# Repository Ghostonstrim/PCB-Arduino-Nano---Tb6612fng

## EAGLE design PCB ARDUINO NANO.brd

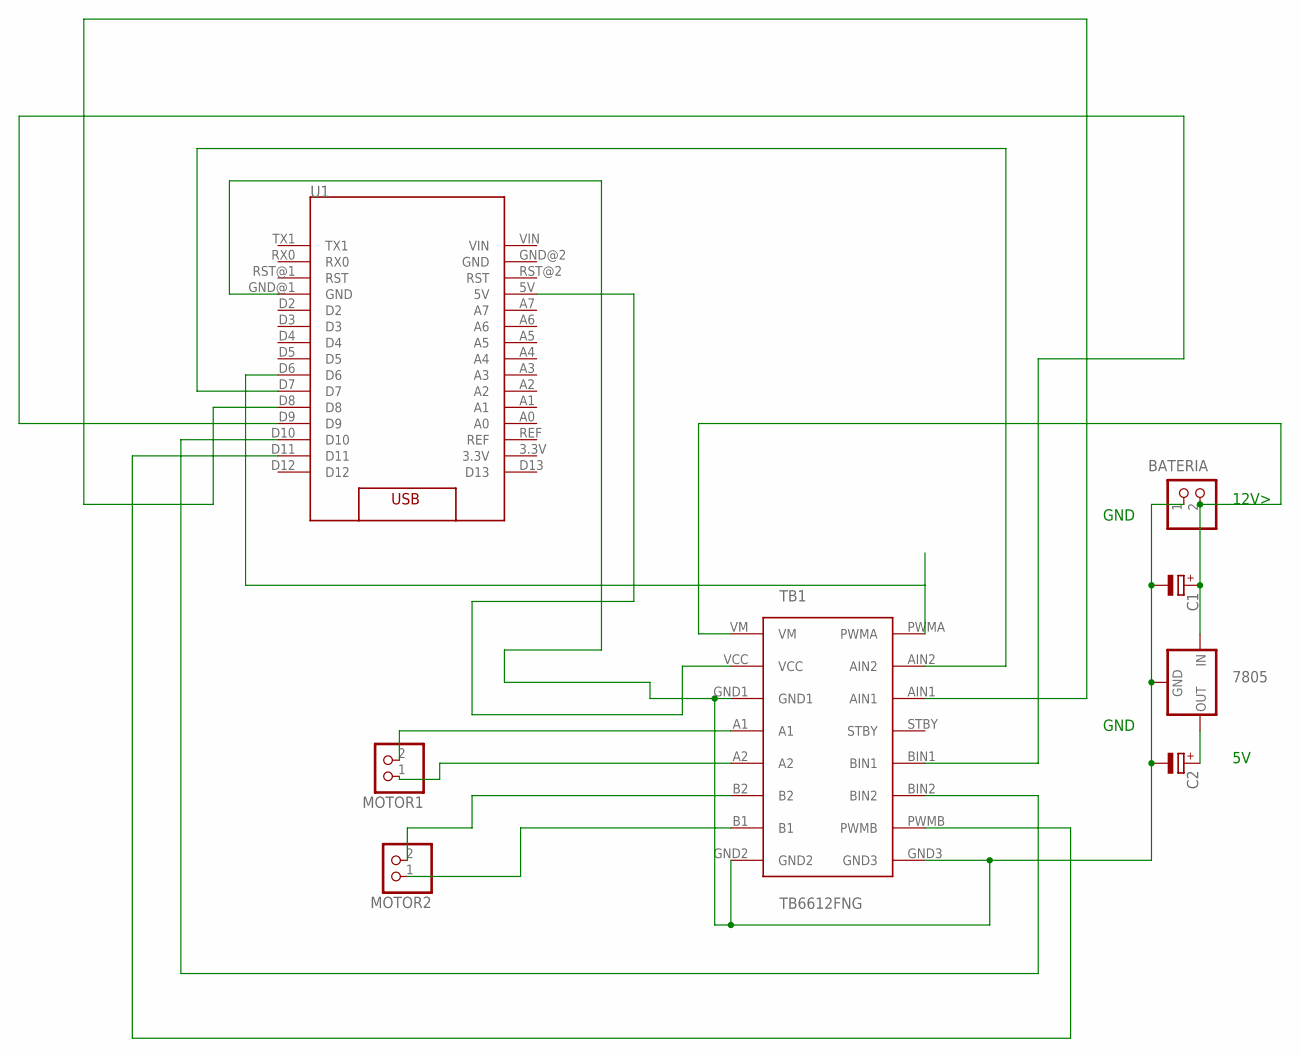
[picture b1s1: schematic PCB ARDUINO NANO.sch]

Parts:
7805: 78XXS
BATERIA: PINHD-1X2; 1X02
C1, C2: CPOL-EUE2.5-6; E2,5-6
MOTOR1, MOTOR2: PINHD-1X2; 1X02
TB1: TB6612FNG
U1: ARDUINO_NANO

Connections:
unnamed: MOTOR1.2, TB1.A1
unnamed: 7805.IN, BATERIA.2, C1.+, TB1.VM
unnamed: 7805.OUT, C2.+
unnamed: TB1.VCC, U1.5V
unnamed: 7805.GND, BATERIA.1, C1.-, C2.-, TB1.GND1, TB1.GND2, TB1.GND3, U1.GND@1 (GND)
unnamed: MOTOR1.1, TB1.A2
unnamed: MOTOR2.2, TB1.B2
unnamed: MOTOR2.1, TB1.B1
unnamed: TB1.PWMA, U1.D6
unnamed: TB1.AIN2, U1.D7
unnamed: TB1.AIN1, U1.D8
unnamed: TB1.BIN1, U1.D9
unnamed: TB1.BIN2, U1.D10
unnamed: TB1.PWMB, U1.D11

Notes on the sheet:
12V>
GND

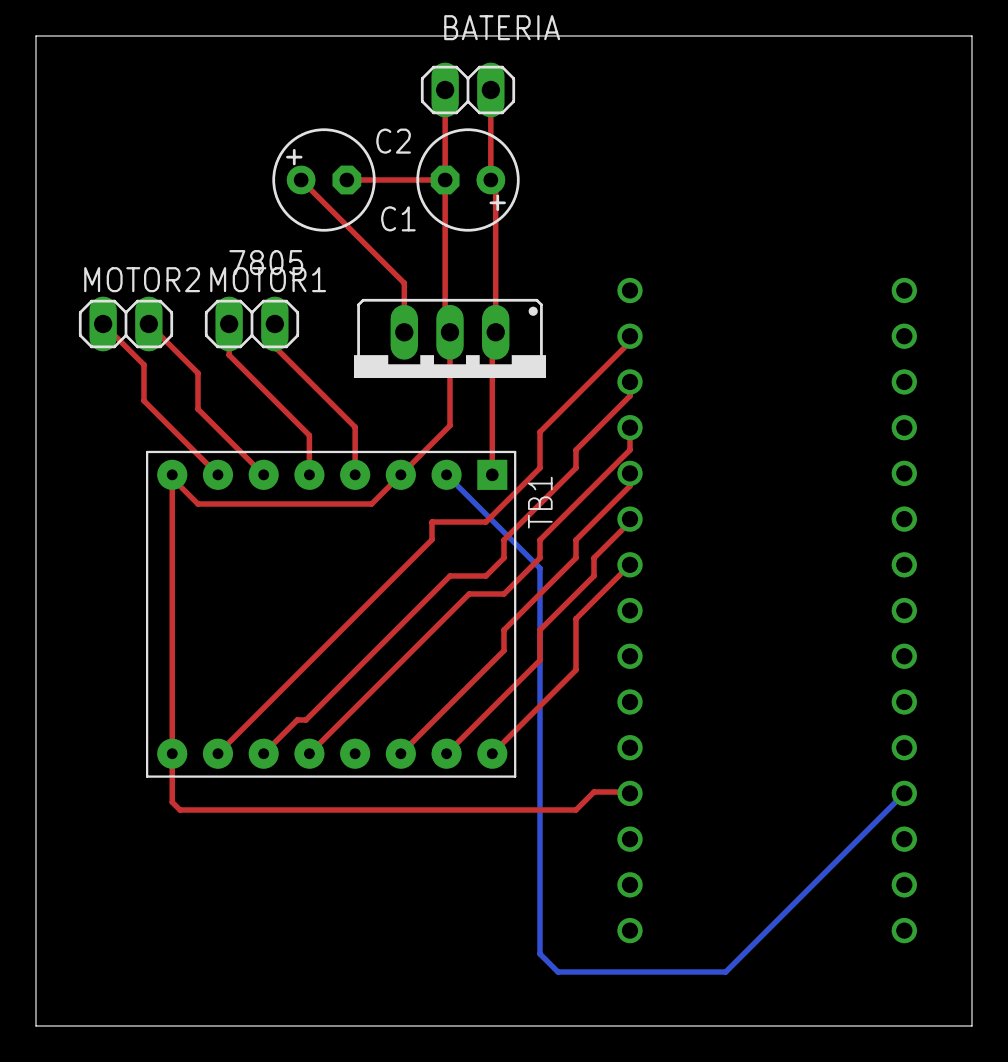
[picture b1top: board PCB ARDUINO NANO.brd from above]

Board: 2 copper layers, 52.0 x 55.0 mm, 8 parts (1 on the bottom side), 14 nets.

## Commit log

2022-08-14 PCB ARDUINO NANO
